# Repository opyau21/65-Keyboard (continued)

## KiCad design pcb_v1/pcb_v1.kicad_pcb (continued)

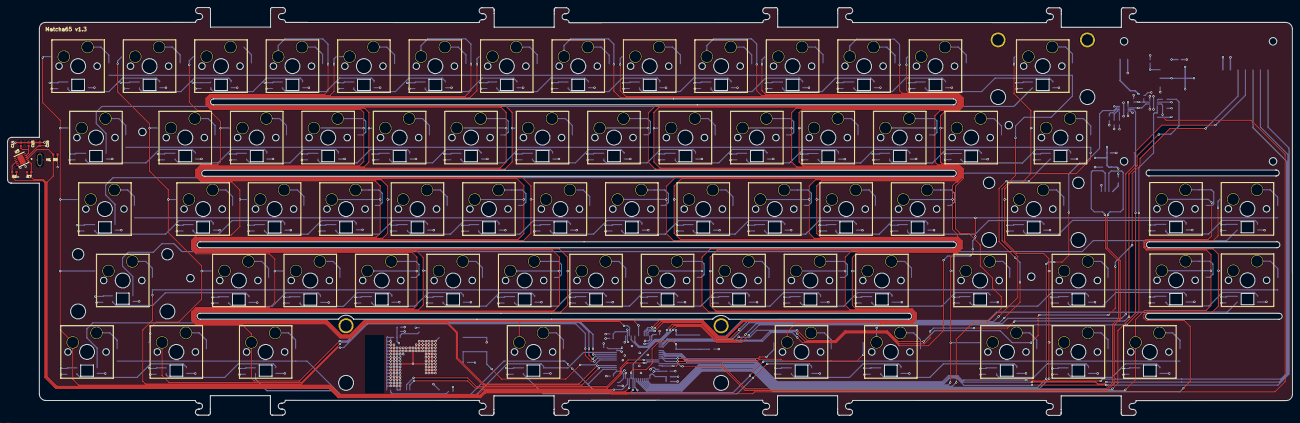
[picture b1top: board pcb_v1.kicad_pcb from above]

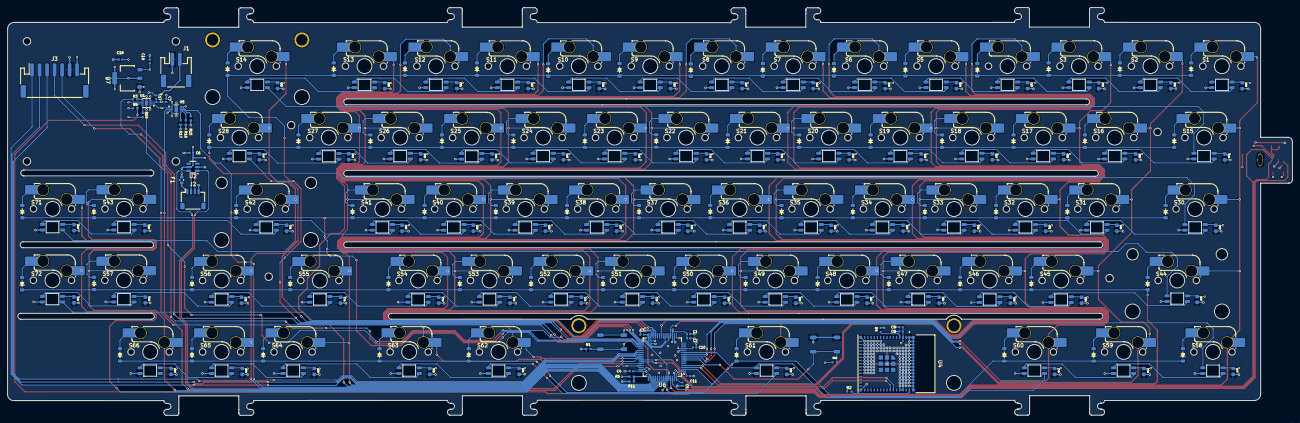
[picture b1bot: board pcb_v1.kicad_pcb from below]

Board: 4 copper layers, 342.6 x 108.7 mm, 318 parts (309 on the bottom side), 185 nets.

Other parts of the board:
C1, C2, C3, C4, C5, C9, C11: 100nF; CAPC1005X55N
C8: 10uF; CAPC1005X55N
C10: 4.7uF; CAPC1005X55N
H1: MountingHole_2.2mm_M2_DIN965_Pad
R2, R4, R5, R11: 10k; RESC1005X40N
U4: ESP32-S3-MINI-1; XCVR_ESP32-S3-MINI-1-N8
U6: STM32F103RETx; LQFP-64_10x10mm_P0.5mm

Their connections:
+3.3V: C1.1, C2.1, C3.1, C4.1, C5.1, C8.1, C9.1, C10.1, C11.1, R2.2, R4.2, U4.3 (3V3), U6.1 (VBAT), U6.13 (VDDA), U6.19 (VDD), U6.32 (VDD), U6.48 (VDD), U6.64 (VDD); also elsewhere on the board
ALERT: U6.34 (PB13); also elsewhere on the board
BOOT0: U6.60 (BOOT0); also elsewhere on the board
CS: U6.37 (PC6); also elsewhere on the board
Column0: U6.62 (PB9); also elsewhere on the board
Column1: U6.9 (PC1); also elsewhere on the board
Column2: U6.10 (PC2); also elsewhere on the board
Column3: U6.3 (PC14); also elsewhere on the board
Column4: U6.4 (PC15); also elsewhere on the board
Column5: U6.20 (PA4); also elsewhere on the board
Column6: U6.25 (PC5); also elsewhere on the board
Column7: U6.28 (PB2); also elsewhere on the board
Column8: U6.29 (PB10); also elsewhere on the board
Column9: U6.40 (PC9); also elsewhere on the board
Column10: U6.41 (PA8); also elsewhere on the board
Column11: U6.51 (PC10); also elsewhere on the board
Column12: U6.52 (PC11); also elsewhere on the board
Column13: U6.54 (PD2); also elsewhere on the board
Column14: U6.56 (PB4); also elsewhere on the board
Column15: U6.57 (PB5); also elsewhere on the board
D+: U6.45 (PA12); also elsewhere on the board
D-: U6.44 (PA11); also elsewhere on the board
DC: U6.38 (PC7); also elsewhere on the board
DIN: U6.23 (PA7); also elsewhere on the board
GND: C1.2, C2.2, C3.2, C4.2, C5.2, C8.2, C9.2, C10.2, C11.2, H1.1, R11.1, U4.1 (GND), U4.2 (GND), U4.42 (GND), U4.43 (GND), U4.46 (GND), U4.47 (GND), U4.48 (GND), U4.49 (GND), U4.50 (GND), U4.51 (GND), U4.52 (GND), U4.53 (GND), U4.54 (GND), U4.55 (GND), U4.56 (GND), U4.57 (GND), U4.58 (GND), U4.59 (GND), U4.60 (GND), U4.61 (GND), U4.62 (GND), U4.63 (GND), U4.64 (GND), U4.65 (GND), U6.12 (VSSA), U6.18 (VSS), U6.31 (VSS), U6.47 (VSS), U6.63 (VSS); also elsewhere on the board
NRST: U6.7 (NRST); also elsewhere on the board
unnamed: R2.1, U4.45 (EN)
unnamed: R4.1, U4.4 (IO0)
unnamed: R5.1, R11.2, U6.50 (PA15)
RDY: U6.61 (PB8); also elsewhere on the board
RGB: U6.11 (PC3); also elsewhere on the board
RST: U6.39 (PC8); also elsewhere on the board
RXTX: U4.39 (TXD0), U6.43 (PA10)
Row0: U6.30 (PB11); also elsewhere on the board
Row1: U6.33 (PB12); also elsewhere on the board
Row2: U6.35 (PB14); also elsewhere on the board
Row3: U6.8 (PC0); also elsewhere on the board
Row4: U6.2 (PC13); also elsewhere on the board
SCL: U6.58 (PB6); also elsewhere on the board
SCLK: U6.21 (PA5); also elsewhere on the board
SDA: U6.59 (PB7); also elsewhere on the board
STAT1: U6.53 (PC12); also elsewhere on the board
STAT2: U6.55 (PB3); also elsewhere on the board
TXRX: U4.40 (RXD0), U6.42 (PA9)
VBUS: R5.2; also elsewhere on the board

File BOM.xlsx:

Item # | Reference | Qty | Manufacturer | Vendor | Mfg Part # | Value | Description/Value | Package | Datasheet
1 | C1, C11, C2, C3, C4, C5, C9 | 6 | Murata Electronics | Mouser | GRM155R71C103KA01J | 100nF | Multilayer Ceramic Capacitors MLCC - SMD/SMT 0.01 uF 16 VDC 10% 0402 X7R | 402 | ~
2 | C10,C15 | 2 | Murata Electronics | Mouser | GRM155R60J475ME47J | 4.7uF | Multilayer Ceramic Capacitors MLCC - SMD/SMT 4.7 uF 6.3 VDC 20% 0402 X5R | 402 | ~
3 | C8,C16 | 2 | Murata Electronics | Mouser | GRM1555C2A101GA01D | 10uF | Multilayer Ceramic Capacitors MLCC - SMD/SMT 0402 10uF 4VDC 20% X6S AEC-Q200 | 402 | ~
4 | C14 | 1 | Murata Electronics | Mouser | GRM1555C2A101GA01D | 100pF | Multilayer Ceramic Capacitors MLCC - SMD/SMT 100 pF 100 VDC 2% 0402 C0G (NP0) | 402 | ~
5 | C17 | 1 | Murata Electronics | Mouser | GRM155R61A104KA01J | 0.1uF | Multilayer Ceramic Capacitors MLCC - SMD/SMT 0.1 uF 10 VDC 10% 0402 X5R | 402 | https://www.mouser.com/datasheet/2/281/1/GRM155R61A104KA01_0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
6 | C6, C7 | 2 | Murata Electronics | Mouser | GXT155R60J105KE01D | 1uF | Multilayer Ceramic Capacitors MLCC - SMD/SMT 0402 6.3VDC 1uF 10% X5R AEC-Q200 | 402
7 | C20,C21,C22,C23,C24,C25,C26,C27,C28,C29,C30,C31,C32,C33,C34,C35,C36,C37,C38,C39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 | 67 | Murata Electronics | Mouser | GCM188R71C104KA37J | 0.1uF | Multilayer Ceramic Capacitors MLCC - SMD/SMT 0.1 uF 16 VDC 10% 0603 X7R AEC-Q200 | 603 | ~
8 | D1,D2,D3,D4,D5,D6,D7,D8,D9,D10,D11,D12,D13,D14,D15,D16,D17,D18,D19,D20,D21,D22,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 | 67 |  | Adafruit |  | D_Small | Adafruit Accessories 1N4148 SMT SOD-123 Diodes - 100 Pack |  | ~
9 | J1 | 1 |  | AliExpress |  | Conn_01x02 |  |  | ~
10 | J2 | 1 |  | AliExpress |  | Conn_01x04 |  |  | ~
11 | J3 | 1 |  | AliExpress |  | Conn_01x07 |  |  | ~
12 | LED1,LED2,LED3,LED4,LED5,LED6,LED7,LED8,LED9,LED10,LED11,LED12,LED13,LED14,LED1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 | 67 |  | AliExpress |  | LED_SK6812MINI |  |  | https://cdn-shop.adafruit.com/product-files/2686/SK6812MINI_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
13 | R1, R11, R12, R17, R3, R5 | 6 | YAGEO | Mouser | RC0402JR-7D10KL | 10k | Thick Film Resistors - SMD 10 kOhms 62.5 mW 0402 5% | 402 | ~
14 | R6,R7,R8,R9,R10 | 5 | YAGEO | Mouser | RC0402FR-7D4K7L | 4.7k | Thick Film Resistors - SMD 4.7 kOhms 62.5 mW 0402 1% | 402 | ~
15 | R15 | 1 | YAGEO | Mouser |  | 1k |  | 402 | ~
16 | R16 | 1 | YAGEO | Mouser |  | 750 |  | 402 | ~
17 | S1,S2,S3,S4,S5,S6,S7,S8,S9,S10,S11,S12,S13,S14,S16,S17,S18,S19,S20,S21,S22,S23,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 | 58 |  | Cannonkeys |  | Keyswitch | Kailh MX Hotswap Sockets - 110 Pack |  | ~
18 | S15,S28 | 2 |  |  |  | Keyswitch |  |  | ~
19 | S30,S55 | 2 |  |  |  | Keyswitch |  |  | ~
20 | S58,S59,S60,S62,S63 | 5 |  |  |  | Keyswitch |  |  | ~
21 | S67 | 1 |  | Divinikey |  | MX_stab | TX Stabilizers
22 | S68,S69 | 2 |  |  |  | MX_stab
23 | S70 | 1 |  |  |  | MX_stab
24 | SW1,SW2 | 2 | E-Switch | Mouser | TL3342F450QG | SW_Push | Tactile Switches 50mA 12VDC Silver Gull Wing |  | ~
25 | U1 | 1 | Analog Devices / Maxim Integrated | Mouser | MAX17048G+T10 | MAX17048G_T10 | Battery Management 3 A 1-Cell/2-Cell Fuel Gauge with ModelGauge
26 | U2 | 1 | Semtech | Mouser | SRV05-4.TCT | SRV05-4 | ESD Protection Diodes / TVS Diodes RAILCLAMP 4-LINE 5V 3K LFREE |  | http://www.onsemi.com/pub/Collateral/SRV05-4-D.PDF
27 | U3 | 1 | Azoteq | Mouser | IQS6243200DNR | IQS624-3200-DNR | Board Mount Motion & Position Sensors 2 x Capacitive, Hall rotation
28 | U4 | 1 | EspressIf | Mouser | ESP32-S3-MINI-1-N8 | ESP32-S3-MINI-1-N8 | Multiprotocol Modules SMD module, ESP32-S3FN8, 8 MB SPI flash, PCB antenna |  | https://www.espressif.com/sites/default/files/documentation/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
29 | U5 | 1 |  | Mouser | BQ25185DLHR | BQ25185DLHR
30 | U6 | 1 | STMicroelectronics | Mouser | STM32F103RET6TR | STM32F103RETx | ARM Microcontrollers - MCU 32BIT Cortex M3 H/D Performance LINE |  | https://www.st.com/resource/en/datasheet/stm32f103re.pdf
31 | U7 | 1 | UMW | Digikey | AMS1117-3.3 | AMS1117-3.3 | 3.3V LDO Regulator
32 | F1 | 1 | Bourns | Mouser | MF-FSMF050X-2 | MF-FSMF050X-2 | Resettable Fuses - PPTC 6V .5A-HD 40A MAX
33 |  | 1 |  | Amazon/AliExpress |  | 5000 mah | 5000 mah Lithium Ion Recharable Battery
34 |  | 1 |  | AliExpress |  | 01x07 JST PH Wire | 01x07 JST PH Wire
35 |  | 1 | aio3 | Cannonkeys |  |  | Unified Daughterboard
36 |  | 1 | Waveshare | Amazon |  | 128 x 128 | 1.5 inch 128 x 128 RGB OLED Screen
37 |  | 1 | Logitech | AliExpress |  |  | Logitech MX Master 3s Side Scroll Component

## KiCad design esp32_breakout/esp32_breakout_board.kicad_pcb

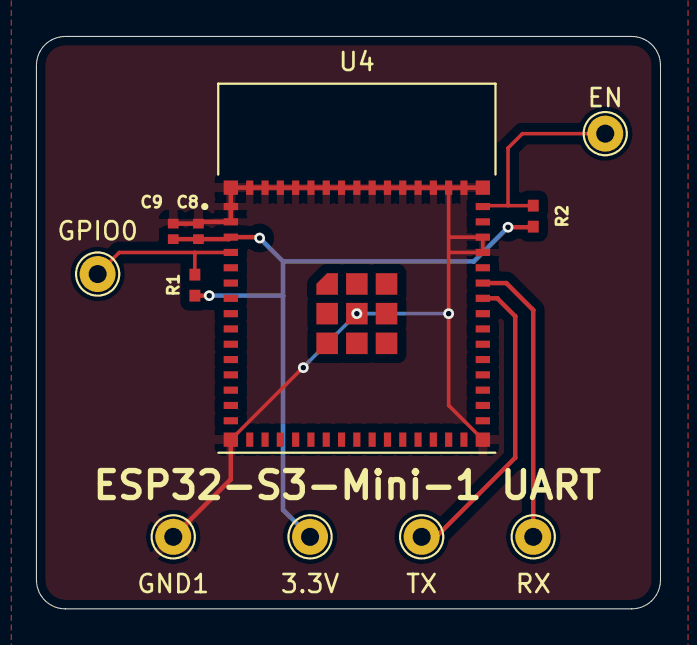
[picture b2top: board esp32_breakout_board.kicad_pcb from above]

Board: 2 copper layers, 34.7 x 31.8 mm, 11 parts (0 on the bottom side), 6 nets.

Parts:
3.3V: TestPoint; TestPoint_THTPad_D2.0mm_Drill1.0mm
C8: 10uF; CAPC1005X55N
C9: 100nF; CAPC1005X55N
EN: TestPoint; TestPoint_THTPad_D2.0mm_Drill1.0mm
GND1: TestPoint; TestPoint_THTPad_D2.0mm_Drill1.0mm
GPIO0: TestPoint; TestPoint_THTPad_D2.0mm_Drill1.0mm
R1, R2: 10k; RESC1005X40N
RX: TestPoint; TestPoint_THTPad_D2.0mm_Drill1.0mm
TX: TestPoint; TestPoint_THTPad_D2.0mm_Drill1.0mm
U4: ESP32-S3-MINI-1; XCVR_ESP32-S3-MINI-1-N8

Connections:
+3.3V: 3.3V.1, C8.1, C9.1, R1.2, R2.2, U4.3 (3V3)
EN: EN.1, R2.1, U4.45 (EN)
GND: C8.2, C9.2, GND1.1, U4.1 (GND), U4.2 (GND), U4.42 (GND), U4.43 (GND), U4.46 (GND), U4.47 (GND), U4.48 (GND), U4.49 (GND), U4.50 (GND), U4.51 (GND), U4.52 (GND), U4.53 (GND), U4.54 (GND), U4.55 (GND), U4.56 (GND), U4.57 (GND), U4.58 (GND), U4.59 (GND), U4.60 (GND), U4.61 (GND), U4.62 (GND), U4.63 (GND), U4.64 (GND), U4.65 (GND)
GPIO0: GPIO0.1, R1.1, U4.4 (IO0)
RX: RX.1, U4.40 (RXD0)
TX: TX.1, U4.39 (TXD0)

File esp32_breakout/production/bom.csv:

Designator,Footprint,Quantity,Value,LCSC Part #
"3.3V, EN, GND1, GPIO0, RX, TX",TestPoint_THTPad_D2.0mm_Drill1.0mm,6,TestPoint,
C8,CAPC1005X55N,1,10uF,C49678
C9,CAPC1005X55N,1,100nF,C49678
"R1, R2",RESC1005X40N,2,10k,
U4,XCVR_ESP32-S3-MINI-1-N8,1,ESP32-S3-MINI-1,

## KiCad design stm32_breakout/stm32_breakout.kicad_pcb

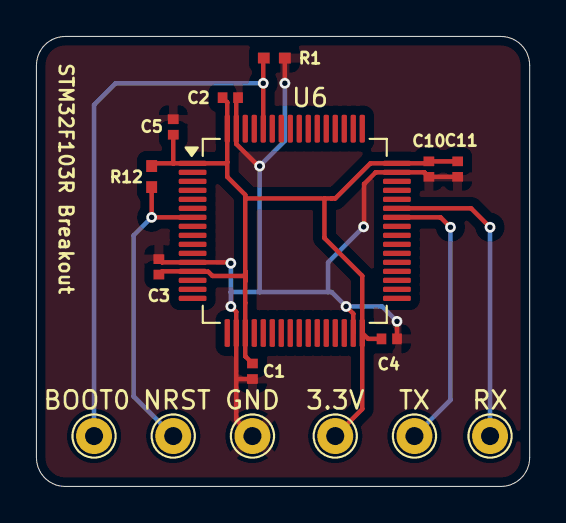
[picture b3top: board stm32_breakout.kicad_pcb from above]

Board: 2 copper layers, 27.4 x 25.0 mm, 16 parts (0 on the bottom side), 6 nets.

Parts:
3.3V: TestPoint; TestPoint_THTPad_D2.0mm_Drill1.0mm
BOOT0: TestPoint; TestPoint_THTPad_D2.0mm_Drill1.0mm
C1, C2, C3, C4, C5, C11: 100nF; CAPC1005X55N
C10: 4.7uF; CAPC1005X55N
GND: TestPoint; TestPoint_THTPad_D2.0mm_Drill1.0mm
NRST: TestPoint; TestPoint_THTPad_D2.0mm_Drill1.0mm
R1, R12: 10k; RESC1005X40N
RX: TestPoint; TestPoint_THTPad_D2.0mm_Drill1.0mm
TX: TestPoint; TestPoint_THTPad_D2.0mm_Drill1.0mm
U6: STM32F103RETx; LQFP-64_10x10mm_P0.5mm

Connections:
+3.3V: 3.3V.1, C1.1, C2.1, C3.1, C4.1, C5.1, C10.1, C11.1, R12.2, U6.1 (VBAT), U6.13 (VDDA), U6.19 (VDD), U6.32 (VDD), U6.48 (VDD), U6.64 (VDD)
BOOT0: BOOT0.1, R1.1, U6.60 (BOOT0)
GND: C1.2, C2.2, C3.2, C4.2, C5.2, C10.2, C11.2, GND.1, R1.2, U6.12 (VSSA), U6.18 (VSS), U6.31 (VSS), U6.47 (VSS), U6.63 (VSS)
NRST: NRST.1, R12.1, U6.7 (NRST)
RX: RX.1, U6.43 (PA10)
TX: TX.1, U6.42 (PA9)

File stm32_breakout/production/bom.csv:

Designator,Footprint,Quantity,Value,LCSC Part #
"3.3V, BOOT0, GND, NRST, RX, TX",TestPoint_THTPad_D2.0mm_Drill1.0mm,6,TestPoint,
"C1, C11, C2, C3, C4, C5",CAPC1005X55N,6,100nF,C49678
C10,CAPC1005X55N,1,4.7uF,C49678
"R1, R12",RESC1005X40N,2,10k,
U6,LQFP-64_10x10mm_P0.5mm,1,STM32F103RETx,

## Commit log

2025-04-06 v1.0 pcb
    Constructed v1.0 of PCB, just 65% layout keys
2025-04-07 Added footprints for LEDs, Rotary Encoder
2025-04-07 Included Capacitors and JST connector in schematic. Upgraded MC to 69 pin version
2025-04-08 Added Flex Cuts
2025-04-08 Re-drew PCB. Flipped to the correct orientation
2025-04-09 Basic Routing around flex cuts
2025-04-10 New LED Schematic
2025-04-10 Replaced and wired LEDs and Capacitors
2025-04-11 Daisy Chained LEDs
2025-04-11 Added 5V connectors to LEDs
2025-04-11 Drew in Main 5V lines
2025-04-11 All 5V LEDs are connected
2025-04-11 Drew Main Ground Line
2025-04-11 Fixed Via Sizes
2025-04-11 Clearance fixes
2025-04-13 Connected all switches, LEDs to MCU
2025-04-13 Routed trace to rotary encoder
2025-04-13 Added Decoupling Capacitors
2025-04-14 Added ESP Protection
2025-04-20 Wiring Update
2025-04-26 New MCU. Added ESP32 S3 Mini1 to act as Bluetooth module
2025-04-28 Updated wiring
2025-04-28 Added basic firmware files for esp32
2025-04-28 Create BOM
2025-04-29 Update Wiring
2025-04-30 Wired all keyboard matrix pins
2025-05-02 Connected OLED pin connector
2025-05-18 Changed Layout of Keyboard
    Row 1, Column 14 Removed due to OLED Screen taking up 2x2 u space
2025-05-19 Finished PCB Framework Design
2025-05-24 Changed PCB to Accommodate Revised Layout
    Added a few more keys to balance the screen being 2u x 2u, therefore extending the length of the PCB
2025-05-29 New Charger IC, Added Ground Plane
2025-05-29 Added Thermal Vias
2025-05-29 Update BOM
2025-05-30 Added initial QMK files
2025-05-30 Added Keymap
2025-06-01 Reposition IQS624
2025-06-07 Updated thru holes and connector sizings
2025-06-12 Finished 4 layer design
2025-06-14 Changed gasket mounts and added keepout zone for esp32
2025-06-17 Added thermal net for AMS1117-3.3
2025-06-19 Reverse polarity on pins
2025-06-20 Made flex cuts longer
2025-06-21 Creation of breakout boards for stm32 and esp32 flashing
2025-06-22 Included resistors for EN/GPIO0 on ESP32
2025-06-24 Update Breakout board designs
2025-06-24 Edited Firmware for ESP32
2025-06-30 esp32 v1.0
2025-06-30 Revived ESP32 Breakout Board
2025-06-30 Updated esp32 breakout board
2025-07-01 Added silkscreen to boards
2025-07-01 Prettied up traces on PCB
2025-07-01 Added Plate Mounting Screw Holes in PCB
2025-07-02 Added more silkscreen to the pcb
2025-07-02 Re-located one screw hole for plate screw
